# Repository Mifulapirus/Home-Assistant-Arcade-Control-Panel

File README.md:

# Home Assistant Control Panel

Home Assistant Control Panel project, including hardware designs and firmware for a smart home interface.

## Project Structure

- **Hardware/** - KiCad PCB designs and schematics
  - `HA Deck 0.1/` - Initial ESP8266-based prototype
  - `HA Deck 1.0/` - Current ESP32-based design
- **Software/** - ESPHome firmware configuration
  - Complete firmware for HA Deck 1.0
  - Setup guides and example automations

## Hardware Versions

### Version 0.1
- Based on **Wemos D1 Mini** (ESP8266)
- Initial prototype design
- KiCad project files located in `Hardware/HA Deck 0.1`

### Version 1.0 (Current Development)
- Based on **ESP32-WROOM-32** module
- Hardware upgrade driven by I/O requirements:
  - 5 arcade buttons with individual LEDs
  - 1.3" OLED I2C display
  - DHT22 temperature/humidity sensor
  - RCWL-0516 motion sensor
  - Buzzer for audio feedback
- KiCad project files located in `Hardware/HA Deck 1.0`
- Firmware located in `Software/`

## Firmware

- **ESPHome** - Used for firmware development and Home Assistant integration
- Enables easy configuration and OTA updates
- Native Home Assistant API support
- Color-coded buttons (Blue, Green, Red, White, Yellow)
- Custom display messages
- 10 buzzer sound patterns
- Full sensor integration

## Technologies Used

- KiCad for PCB design
- ESP32-WROOM-32 module (Version 1.0)
- Wemos D1 Mini / ESP8266 (Version 0.1)
- ESPHome firmware framework
- Home Assistant integration

## Getting Started

### Hardware
1. Open KiCad project files in `Hardware/HA Deck 1.0/`
2. Review schematic and PCB layout
3. Export Gerber files for fabrication

### Firmware
1. Navigate to `Software/` directory
2. Follow instructions in `ESPHOME_SETUP.md`
3. Configure `secrets.yaml` with your WiFi credentials
4. Upload firmware to ESP32

## Deployment

1. Fabricate the PCB using exported Gerber files
2. Assemble components according to schematic
3. Flash ESPHome firmware via USB
4. Device auto-discovers in Home Assistant
5. Configure automations and integrations

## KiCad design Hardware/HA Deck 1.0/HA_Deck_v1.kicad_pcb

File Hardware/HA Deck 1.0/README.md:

# HA Deck v1.0 - Hardware Documentation

Home Assistant Control Deck Version 1.0 with ESP32-WROOM-32

## Hardware Overview

### Microcontroller
- **ESP32-WROOM-32** (NodeMCU Dev Board)
- Dual-core 240 MHz processor
- Built-in WiFi and Bluetooth
- 3.3V logic level

### Components

#### User Interface
- **5× Arcade Style Buttons** - User input controls
- **5× LEDs** - Individual button illumination (one per button)
- **1.3" OLED I2C Display** - Status and information display
- **Buzzer** - Audio feedback

#### Sensors
- **DHT22** - Temperature and humidity sensor
- **RCWL-0516** - Microwave radar motion sensor

## Pin Assignment

### Buttons (Digital Input with Internal Pull-ups)
| Component | GPIO Pin | Notes |
|-----------|----------|-------|
| Button 1  | GPIO17   | Active LOW |
| Button 2  | GPIO19   | Active LOW |
| Button 3  | GPIO33   | Active LOW |
| Button 4  | GPIO26   | Active LOW |
| Button 5  | GPIO27   | Active LOW |

### LEDs (Digital Output)
| Component | GPIO Pin | Current Limiting |
|-----------|----------|------------------|
| LED 1     | GPIO16   | 220Ω resistor |
| LED 2     | GPIO18   | 220Ω resistor |
| LED 3     | GPIO32   | 220Ω resistor |
| LED 4     | GPIO25   | 220Ω resistor |
| LED 5     | GPIO14   | 220Ω resistor |

### I2C Display
| Function | GPIO Pin | Notes |
|----------|----------|-------|
| SDA      | GPIO21   | Default I2C data |
| SCL      | GPIO22   | Default I2C clock |

### Sensors
| Component    | GPIO Pin | Function |
|--------------|----------|----------|
| DHT22        | GPIO04   | Digital data line |
| RCWL-0516    | GPIO23   | Digital output |

### Audio
| Component | GPIO Pin | Notes |
|-----------|----------|-------|
| Buzzer    | GPIO13   | PWM capable |

### Power
- **VCC**: 3.3V for logic-level components
- **VIN**: 5V for sensors requiring higher voltage (DHT22, RCWL-0516)
- **GND**: Common ground

## Circuit Design Notes

### Button Configuration
- Buttons wired between GPIO and GND
- Internal pull-up resistors enabled in firmware (no external resistors needed)
- Debouncing handled in software

### LED Configuration
- Each LED in series with 220Ω current-limiting resistor
- Connected between GPIO and GND
- Forward voltage: ~2V, forward current: ~5-10mA

### I2C Display
- Standard I2C interface
- 3.3V compatible
- Address: Typically 0x3C or 0x3D

### Sensors
- **DHT22**: Single-wire digital interface, requires 3.3-5V
- **RCWL-0516**: 4-28V input, 3.3V compatible output

## Firmware

### Platform
- **ESPHome** - YAML configuration for Home Assistant integration

### Key Features
- Native Home Assistant API
- OTA (Over-The-Air) updates
- Real-time sensor monitoring
- Button press events
- LED control
- Display management

## GPIO Usage Summary

**Total GPIOs Used: 15**
- 5× Button inputs
- 5× LED outputs
- 2× I2C (shared bus)
- 1× DHT22 sensor
- 1× Motion sensor
- 1× Buzzer

**Available for expansion:** GPIO pins still available for future features

## Design Decisions

### Why ESP32-WROOM-32 over ESP8266?
The ESP32 was chosen over the ESP8266 (used in v0.1) due to:
- **GPIO count**: Need 13+ GPIOs for all components
- **Processing power**: Dual-core for better multitasking
- **Native I2C**: Better support for multiple I2C devices
- **Future expansion**: Additional pins available

### Pin Selection Rationale
- Avoided boot-sensitive pins (GPIO0, GPIO2, GPIO5, GPIO12, GPIO15)
- Used default I2C pins (GPIO21/22) for reliability
- Selected general-purpose pins for buttons (GPIO17, 19, 33, 26, 27) to enable internal pull-ups
- Distributed LED pins across available GPIOs (GPIO16, 18, 32, 25, 14)
- PWM-capable pins used for buzzer (GPIO13) and LED control
- Sensor pins carefully selected to avoid conflicts (GPIO04, GPIO23)

## Files in This Directory

- `HA_Deck_v1.kicad_pro` - KiCad project file
- `HA_Deck_v1.kicad_sch` - Schematic design
- `HA_Deck_v1.kicad_pcb` - PCB layout
- `README.md` - This file

**Firmware files are located in:** `../../Software/`

## Development Status

- [x] Component selection
- [x] Pin assignment
- [x] Initial schematic created
- [x] ESPHome firmware configuration
- [ ] Complete schematic wiring
- [ ] PCB layout design
- [ ] Footprint assignment
- [ ] PCB fabrication
- [ ] Assembly and testing

## Version History

**v1.0** (2026-02-07)
- Initial design with ESP32-WROOM-32
- 5 buttons with individual LEDs
- OLED display, DHT22, RCWL-0516 sensors
- Buzzer for audio feedback

---

*For main project information, see the [root README](../../README.md)*

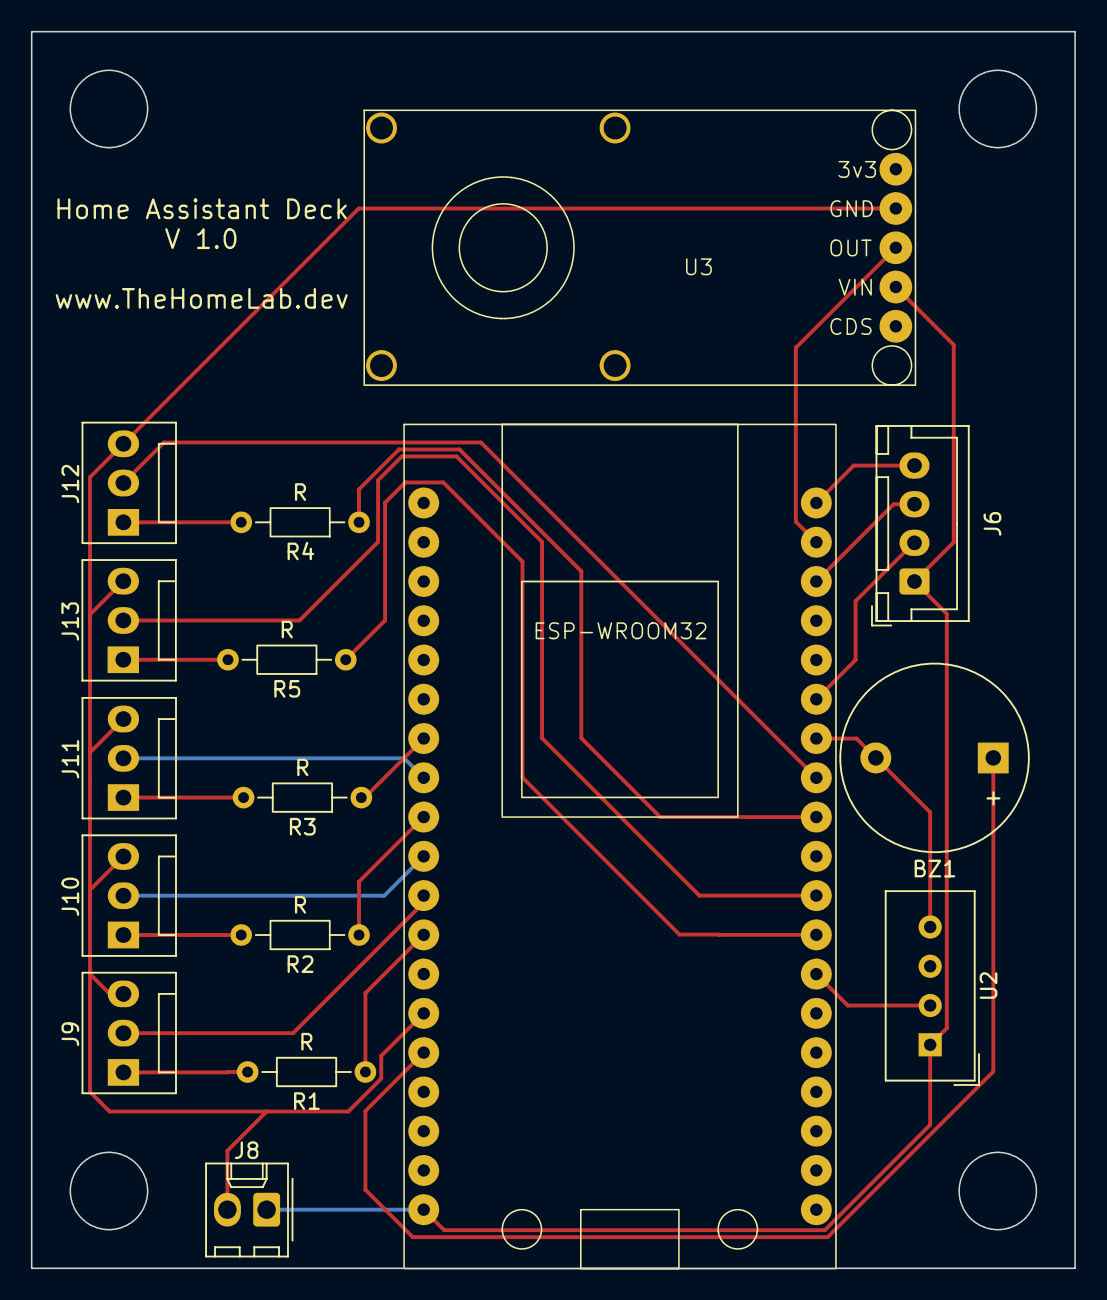
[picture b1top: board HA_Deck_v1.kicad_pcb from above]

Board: 2 copper layers, 67.5 x 80.0 mm, 16 parts (0 on the bottom side), 22 nets.

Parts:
BZ1: Buzzer; Buzzer_12x9.5RM7.6
J6: Conn_01x04_Pin; JST_XH_B4B-XH-A_1x04_P2.50mm_Vertical
J8: Conn_01x02; Molex_KK-254_AE-6410-02A_1x02_P2.54mm_Vertical
J9, J10, J11, J12, J13: Conn_01x03_Pin; FanPinHeader_1x03_P2.54mm_Vertical
R1, R2, R3, R4, R5: R; R_Axial_DIN0204_L3.6mm_D1.6mm_P7.62mm_Horizontal
U1: ESP32-WROOM-NODEMCU; ESP32-Wroom-NodeMCU
U2: DHT11; Aosong_DHT11_5.5x12.0_P2.54mm
U3: RCWL-0516

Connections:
+5V: J6.1, J8.1, U1.1 (5V), U2.1 (VDD), U3.4 (VIN)
GND: BZ1.2 (-), J6.4, J8.2, J9.3, J10.3, J11.3, J12.3, J13.3, U1.6 (GND), U2.4 (GND), U3.2 (GND)
unnamed: BZ1.1 (+), U1.5 (GPIO13)
unnamed: J6.2, U1.33 (I2C_SDA/GPIO21)
unnamed: J6.3, U1.36 (I2C_SCL/GPIO22)
unnamed: J9.1, R1.2
unnamed: J9.2, U1.9 (GPIO27)
unnamed: J10.1, R2.2
unnamed: J10.2, U1.10 (GPIO26)
unnamed: J11.1, R3.2
unnamed: J11.2, U1.12 (GPIO33)
unnamed: J12.1, R4.2
unnamed: J12.2, U1.31 (GPIO19)
unnamed: J13.1, R5.2
unnamed: J13.2, U1.28 (TX2/GPIO17)
unnamed: U1.26 (GPIO04), U2.2 (DATA)
unnamed: R1.1, U1.8 (GPIO14)
unnamed: R4.1, U1.30 (GPIO18)
unnamed: U1.37 (GPIO23), U3.3 (OUT)
unnamed: R2.1, U1.11 (GPIO25)
unnamed: R3.1, U1.13 (GPIO32)
unnamed: R5.1, U1.27 (RX2/GPIO16)

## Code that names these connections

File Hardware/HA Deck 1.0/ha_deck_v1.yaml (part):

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
# I2C Bus for OLED Display
i2c:
  sda: GPIO21
  scl: GPIO22
  scan: true
  id: bus_a

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# DHT22 Temperature and Humidity Sensor
sensor:
  - platform: dht
    pin: GPIO04
    model: DHT22
    temperature:
      name: "Arcade Panel Temperature"
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  # Blue Button
  - platform: gpio
    pin:
      number: GPIO17
      mode:
        input: true
        pullup: true
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  # Green Button
  - platform: gpio
    pin:
      number: GPIO19
      mode:
        input: true
        pullup: true
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  # Red Button
  - platform: gpio
    pin:
      number: GPIO33
      mode:
        input: true
        pullup: true
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  # White Button
  - platform: gpio
    pin:
      number: GPIO26
      mode:
        input: true
        pullup: true
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  # Yellow Button
  - platform: gpio
    pin:
      number: GPIO27
      mode:
        input: true
        pullup: true
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  
  # RCWL-0516 Motion Sensor
  - platform: gpio
    pin: GPIO23
    name: "Arcade Panel Motion"
    device_class: motion
    id: motion_sensor
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# Output for Buzzer
output:
  - platform: gpio
    pin: GPIO13
    id: buzzer_output

# LED Outputs
  - platform: gpio
    pin: GPIO16
    id: output_blue
  
  - platform: gpio
    pin: GPIO18
    id: output_green
  
  - platform: gpio
    pin: GPIO32
    id: output_red
  
  - platform: gpio
    pin: GPIO25
    id: output_white
  
  - platform: gpio
    pin: GPIO14
    id: output_yellow

# Light entities for LEDs
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
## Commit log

2026-02-13 First release
2026-02-13 updated sw
2026-02-13 fixed
2026-02-13 Added pictures
